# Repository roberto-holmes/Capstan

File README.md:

# Specifications

## v1

- USB HID scroll wheel
- BT HID scroll wheel
- Battery Charging with protections:
  - Overvoltage
  - Undervoltage
  - Overcurrent
  - Over temp
  - Reverse battery protection
- Motor

## Future

- FFB
- High resolution scrolling
- Set battery charge level limits
- Load sharing/Power path
- Coulomb counting

- LSE for STM32?

## RF

- Is this antenna suitable?
- Do we need two pi filters?
- Are the pi filter values a good start point?
- Do we need test points for calibration?

# Review Notes 2025/08/11

- ~~move the motor current sense from low side to the switched line~~
- ~~current sensor is 680uA - too high for long term storage (ok?)~~
  - Low power is not priority at the moment
- ~~why 27 ohm gate resistors? suggest 6V/600mA = 10ohm~~
  - Max gate driver current is 250mA
- add decouple to +2V5
- ~~lower the Hall effect sensor data series resistor, suggest 100ohm~~
  - Setting R46 to be DNP instead
- ~~USB diode protection U2 is connected wrong~~
- ~~recommend use TPS61041 rather than TPS61040 (250mA peak rather than 400mA peak - we don't need that much)~~
- ~~C18 is far too high ( I think 33pF ok )~~
  - Using 10pF as recommended by datasheet

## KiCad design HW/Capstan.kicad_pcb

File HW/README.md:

MCU:
STM32WB55CG

- 'C' variant is the smallest, will ikely not need the additional pins of the 'R' or 'V' variants
- 'G' for maximum flash (1MB)

Using [Raspberry Pi Debug Connector Spec](https://datasheets.raspberrypi.com/debug/debug-connector-specification.pdf)

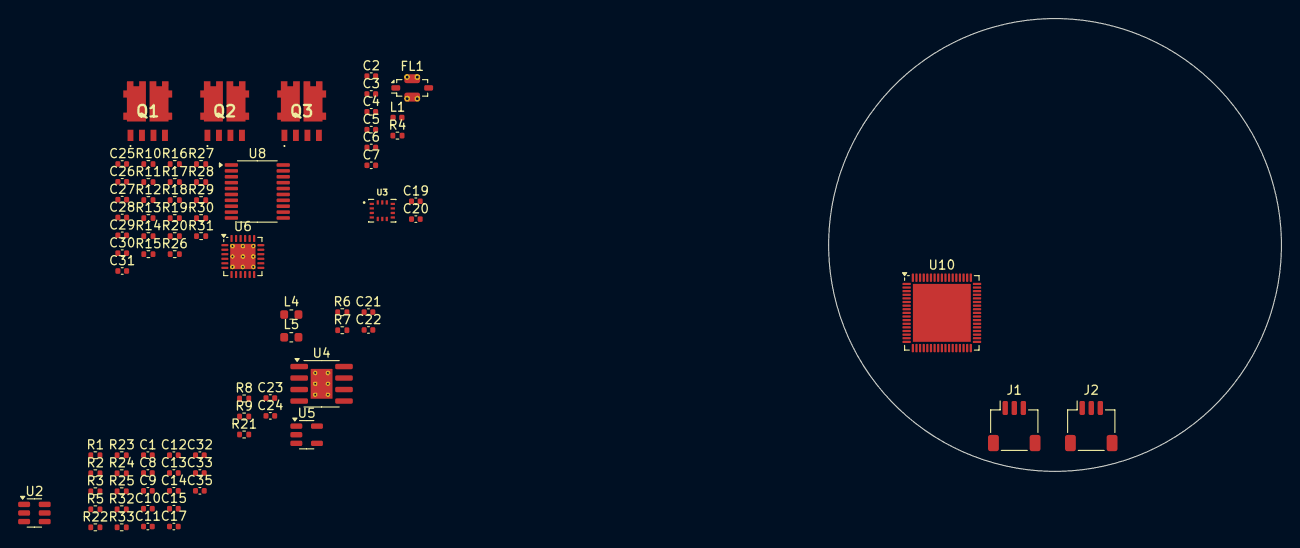
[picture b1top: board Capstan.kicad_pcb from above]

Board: 2 copper layers, 50.0 x 50.0 mm, 81 parts (0 on the bottom side), 57 nets, no tracks yet.

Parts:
C1, C8, C9, C10, C11, C12, C13, C14, C19, C20, C25, C26, C27, C28, C33, C35: 100nF; C_0402_1005Metric
C2: 0.8pF; C_0402_1005Metric
C3: 0.3pF; C_0402_1005Metric
C4: 0.4pF; C_0402_1005Metric
C5: 0.2pF; C_0402_1005Metric
C6, C7: C_0402_1005Metric
C15: 100pF; C_0402_1005Metric
C17, C32: 4.7uF; C_0402_1005Metric
C21, C22: 10uF; C_0402_1005Metric
C23, C24: 1uF; C_0402_1005Metric
C29: CREG12; C_0402_1005Metric
C30, C31: 1nF; C_0402_1005Metric
FL1: BFCN-2450; Filter_Mini-Circuits_FV1206-4
J1: SWD; JST_SH_SM03B-SRSS-TB_1x03-1MP_P1.00mm_Horizontal
J2: UART; JST_SH_SM03B-SRSS-TB_1x03-1MP_P1.00mm_Horizontal
L1: 2.7nH; L_0402_1005Metric
L4: 10uH; L_0603_1608Metric
L5: FCM1608KF-601T03; L_0603_1608Metric
Q1, Q2, Q3: STL40DN3LLH5
R1, R25: 18kΩ; R_0402_1005Metric
R2, R22: 24kΩ; R_0402_1005Metric
R3: 56kΩ; R_0402_1005Metric
R4: 0Ω; R_0402_1005Metric
R5, R11, R18, R20: 10kΩ; R_0402_1005Metric
R6: 2.2kΩ; R_0402_1005Metric
R7, R8: 1kΩ; R_0402_1005Metric
R9: 0.4Ω; R_0402_1005Metric
R10, R17, R26, R27, R29, R30: 27Ω; R_0402_1005Metric
R12, R13, R14, R15: kΩ; R_0402_1005Metric
R16: 39kΩ; R_0402_1005Metric
R19, R28, R31: 12.5mΩ; R_0402_1005Metric
R21: 125mΩ; R_0402_1005Metric
R23, R24, R32, R33: 100Ω; R_0402_1005Metric
U2: USBLC6-2SC6; SOT-23-6
U3: BMI270; XDCR_BMI270
U4: TP4056-42-ESOP8; SOIC-8-1EP_3.9x4.9mm_P1.27mm_EP2.41x3.3mm_ThermalVias
U5: AP2112K-3.3; SOT-23-5
U6: STDRIVE101; QFN-24-1EP_4x4mm_P0.5mm_EP2.8x2.8mm_ThermalVias
U8: INA4181A1; TSSOP-20_4.4x6.5mm_P0.65mm
U10: STM32WB55RGVx; QFN-68-1EP_8x8mm_P0.4mm_EP6.4x6.4mm

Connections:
+2V5: R2.2, U8.20 (REF), U10.13 (VREF+)
+3V3: C9.1, C10.1, C11.1, C12.1, C13.1, C14.1, C15.1, C17.1, C19.1, C20.1, C24.1, C31.1, C33.2, L5.1, R11.2, R12.2, R16.2, U3.5 (VDDIO), U3.8 (VDD), U5.5 (VOUT), U8.5 (VS), U10.1 (VBAT), U10.30 (VDD), U10.33 (VDDRF), U10.44 (VDDSMPS), U10.45 (VDD), U10.55 (VDDUSB), U10.68 (VDD)
+BATT: C8.1, Q1.6 (D), Q2.6 (D), Q3.6 (D), R21.2, R22.2, U8.18 (-)
/MCU/BOOT0: R5.2, U10.5 (PH3)
/MCU/MCU_D+: U2.1 (I/O1), U10.53 (PA12)
/MCU/MCU_D-: U2.3 (I/O2), U10.52 (PA11)
/MCU/SWDCLK: J1.1, R24.2
/MCU/SWDIO: J1.3, R23.2
/MCU/UART_RX: J2.1, R33.2
/MCU/UART_TX: J2.3, R32.2
/MCU/~RST: C1.1, U10.8 (NRST)
/Motor/A: C25.1, Q1.1 (S), Q1.5 (D), Q2.1 (S), Q2.5 (D), Q3.1 (S), Q3.5 (D), U6.23 (OUT1)
/Motor/GHS1: R17.1, R26.1, R29.1, U6.22 (GHS1)
/Motor/GLS1: R10.1, R27.1, R30.1, U6.24 (GLS1)
/Motor/SENSE_1: U8.2, U8.8, U8.13
/Motor/SHS2: C27.2, U6.19 (OUT2)
/Motor/SHS3: C26.2, U6.15 (OUT3)
/Motor/VREF: U8.1 (REF), U8.9 (REF), U8.12 (REF)
/Motor/~FAULT: R16.1, U6.6 (NFAULT)
/RF/RF: C2.1, L1.1
GND: C1.2, C2.2, C3.2, C5.2, C6.2, C7.2, C8.2, C9.2, C10.2, C11.2, C12.2, C13.2, C14.2, C15.2, C17.2, C19.2, C20.2, C22.2, C23.2, C24.2, C28.2, C29.2, C30.2, C31.2, C32.2, C33.1, C35.2, FL1.2 (GND), FL1.4 (GND), J1.2, J2.2, R1.1, R5.1, R6.1, R19.1, R20.1, R25.1, R28.1, R31.1, U2.2 (GND), U3.6 (GNDIO), U3.7 (GND), U4.3 (GND), U4.9 (EPAD), U5.2 (GND), U6.2 (DT/MODE), U6.25 (GND), U8.3 (-), U8.7 (-), U8.14 (-), U8.16 (GND), U10.32 (VSSRF), U10.42 (VSSSMPS), U10.69 (VSS)
unnamed: C5.1, C6.1, R4.2
unnamed: C22.1, U4.5 (BAT)
unnamed: C4.1, C7.1, R4.1
unnamed: C21.1, R9.1, U4.4 (V_{CC}), U4.8 (CE)
unnamed: C3.1, FL1.1 (IN), L1.2
unnamed: C4.2, FL1.3 (OUT)
unnamed: Q1.2 (G), R26.2
unnamed: Q1.4 (G), R27.2
unnamed: Q1.3 (S), R28.2, U8.6 (+)
unnamed: Q2.2 (G), R17.2
unnamed: Q2.4 (G), R10.2
unnamed: Q2.3 (S), R19.2, U8.4 (+)
unnamed: Q3.2 (G), R29.2
unnamed: Q3.4 (G), R30.2
unnamed: Q3.3 (S), R31.2, U8.15 (+)
unnamed: R6.2, U4.2 (PROG)
unnamed: R7.1, U4.7 (~CHRG)
unnamed: R8.1, U4.6 (~STDBY)
unnamed: C23.1, R21.1, U5.1 (VIN), U5.3 (EN), U8.17 (+)
unnamed: C25.2, U6.21 (BOOT1)
unnamed: C27.1, U6.17 (BOOT2)
unnamed: C26.1, U6.13 (BOOT3)
unnamed: C30.1, R12.1, R13.2, R14.2, R15.2, U6.1 (CP)
unnamed: R11.1, U6.3 (SCREF)
unnamed: R18.1, R20.2
unnamed: R22.1, R25.2, U10.15 (PA0)
unnamed: R1.2, R2.1, U10.16 (PA1)
unnamed: R32.1, U10.17 (PA2)
unnamed: R33.1, U10.18 (PA3)
unnamed: R23.1, U10.54 (PA13)
unnamed: R24.1, U10.56 (PA14)
unnamed: C35.1, L5.2, U10.14 (VDDA)
unnamed: C32.1, L4.2, U10.41 (VFBSMPS)
unnamed: L4.1, U10.43 (VLXSMPS)
VBUS: R3.2, R9.2, U2.5 (VBUS)
VS: C28.1, C29.1, U6.4 (VS), U6.5 (REG12)

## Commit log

2025-06-08 Added a start at schematic design
2025-07-14 Almost first schematic draft (missing resistor values for STDRIVE current sensing and leds)
2025-07-14 Added ioc file with MCU config (aprat from SPI2 which should be open drain)
2025-07-26 Added resistor values for LED and removed STDRIVE current sensing
2025-09-21 Added notes from review
2025-09-21 Fixed USB ESD protection
2025-12-19 Cleaned up and implemented some of Laimonas' feedback
